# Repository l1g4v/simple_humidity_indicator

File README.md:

# Simple humidity indicator

This is a really simple board with code whose job is to show the temperature and relative humidity on a 128x32 OLED screen

(very important note: for the KiCAD project you need this symbol and footprint library https://gitlab.fabcloud.org/pub/libraries/electronics/kicad)

The board is actually really simple

I had to do this easy millable so this only uses big components with decent trace sizes and pads

## How it works

After you connect the OLED, DHT and power it up with voltages from 3.3V to 5.2V; It will show you the temperature and relative humidity of the surroundings on the screen, after that the MCU will go to sleep mode for 8 seconds approx(the internal 8MHz clock from the atmega328p is not really precise) and a watchdog will wake it up for the next refresh

## A few notes about the case

At board/case there are the files for 3d printing the case and the Fusion360 project in case someone wants to modify it.
If the case does not fit, print the bottom with 102% XY size and the lid with 101.5% XY size

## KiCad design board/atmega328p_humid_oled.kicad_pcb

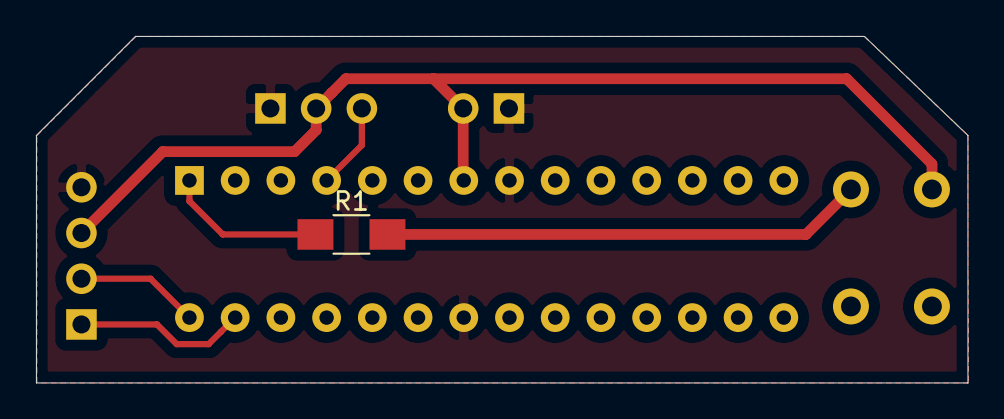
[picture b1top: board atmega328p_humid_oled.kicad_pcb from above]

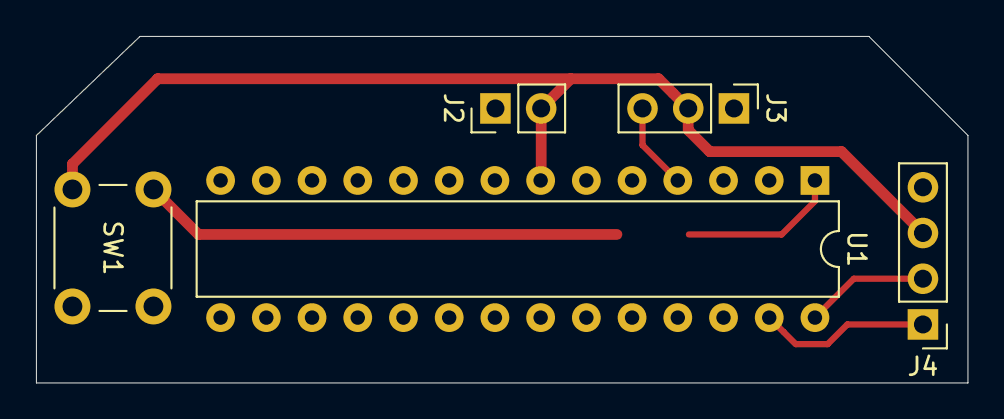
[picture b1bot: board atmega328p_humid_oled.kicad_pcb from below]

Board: 2 copper layers, 51.8 x 19.2 mm, 6 parts (5 on the bottom side), 7 nets.

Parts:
J2: VCC; PinHeader_1x02_P2.54mm_Vertical
J3: DHT; PinHeader_1x03_P2.54mm_Vertical
J4: OLED; PinHeader_1x04_P2.54mm_Vertical
R1: 10K; R_1206
SW1: RESET; SW_PUSH_6mm
U1: ATmega328-PU; DIP-28_W7.62mm

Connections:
+5V: J2.2, J3.2, J4.3, SW1.1, U1.7
GND: J2.1, J3.1, J4.4, U1.8, U1.22
unnamed: J3.3, U1.4
unnamed: J4.1, U1.27
unnamed: J4.2, U1.28
unnamed: R1.1, U1.1
unnamed: R1.2, SW1.2

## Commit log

2021-07-04 first upload
